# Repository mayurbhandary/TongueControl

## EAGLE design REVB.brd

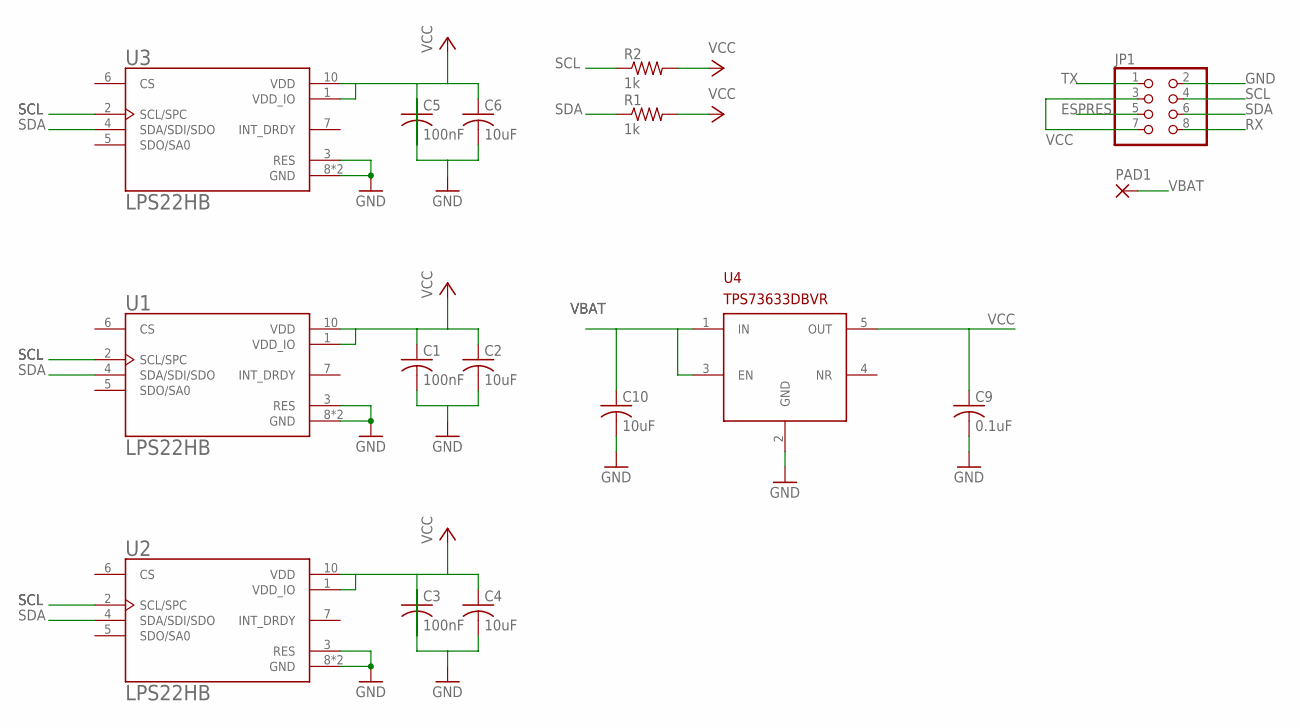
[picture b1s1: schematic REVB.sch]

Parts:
C1, C3, C5: 100nF; C0402
C2, C4, C6, C10: 10uF; C0402
C9: 0.1uF; C0402
JP1: PINHD-2X4/90; 2X04/90
PAD1: 2,15/1,0
R1, R2: 1k; R0402
U1, U2, U3: LPS22HB; LGA10R50P2X3_200X200X80
U4: TPS73633DBVR; SOT23-DBV

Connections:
GND: C1.2, C2.2, C3.1, C4.2, C5.1, C6.2, C9.2, C10.2, JP1.2, U1.3 (RES), U1.8 (GND), U1.9 (GND), U2.3 (RES), U2.8 (GND), U2.9 (GND), U3.3 (RES), U3.8 (GND), U3.9 (GND), U4.2 (GND); also elsewhere on the board
SCL: JP1.4, R2.1, U1.2 (SCL/SPC), U2.2 (SCL/SPC), U3.2 (SCL/SPC); also elsewhere on the board
SDA: JP1.6, R1.1, U1.4 (SDA/SDI/SDO), U2.4 (SDA/SDI/SDO), U3.4 (SDA/SDI/SDO); also elsewhere on the board
VBAT: C10.1, PAD1.1, U4.1 (IN), U4.3 (EN)
VCC: C1.1, C2.1, C3.2, C4.1, C5.2, C6.1, C9.1, JP1.3, JP1.7, R1.2, R2.2, U1.1 (VDD_IO), U1.10 (VDD), U2.1 (VDD_IO), U2.10 (VDD), U3.1 (VDD_IO), U3.10 (VDD), U4.5 (OUT); also elsewhere on the board

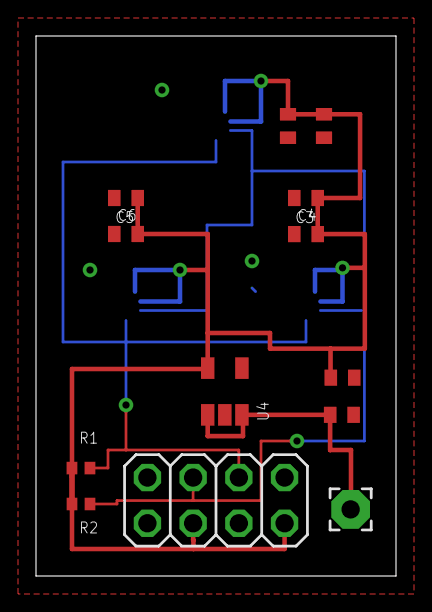
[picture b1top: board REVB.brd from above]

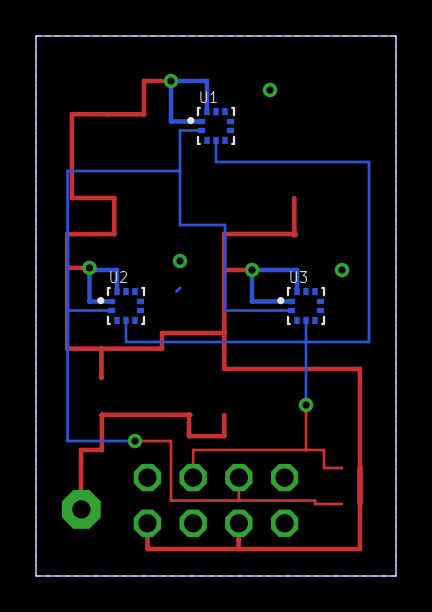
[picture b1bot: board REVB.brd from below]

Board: 2 copper layers, 20.0 x 30.0 mm, 16 parts (3 on the bottom side), 5 nets.

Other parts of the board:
JP2: 2X04

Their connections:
GND: JP2.7; also elsewhere on the board
SCL: JP2.5; also elsewhere on the board
SDA: JP2.3; also elsewhere on the board
VCC: JP2.2, JP2.6; also elsewhere on the board
